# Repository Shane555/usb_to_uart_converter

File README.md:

2 layer USB to UART converter, bread and butter of embedded software for debug logs, flashing via serial etc. Gerber files can be used to generate PCB

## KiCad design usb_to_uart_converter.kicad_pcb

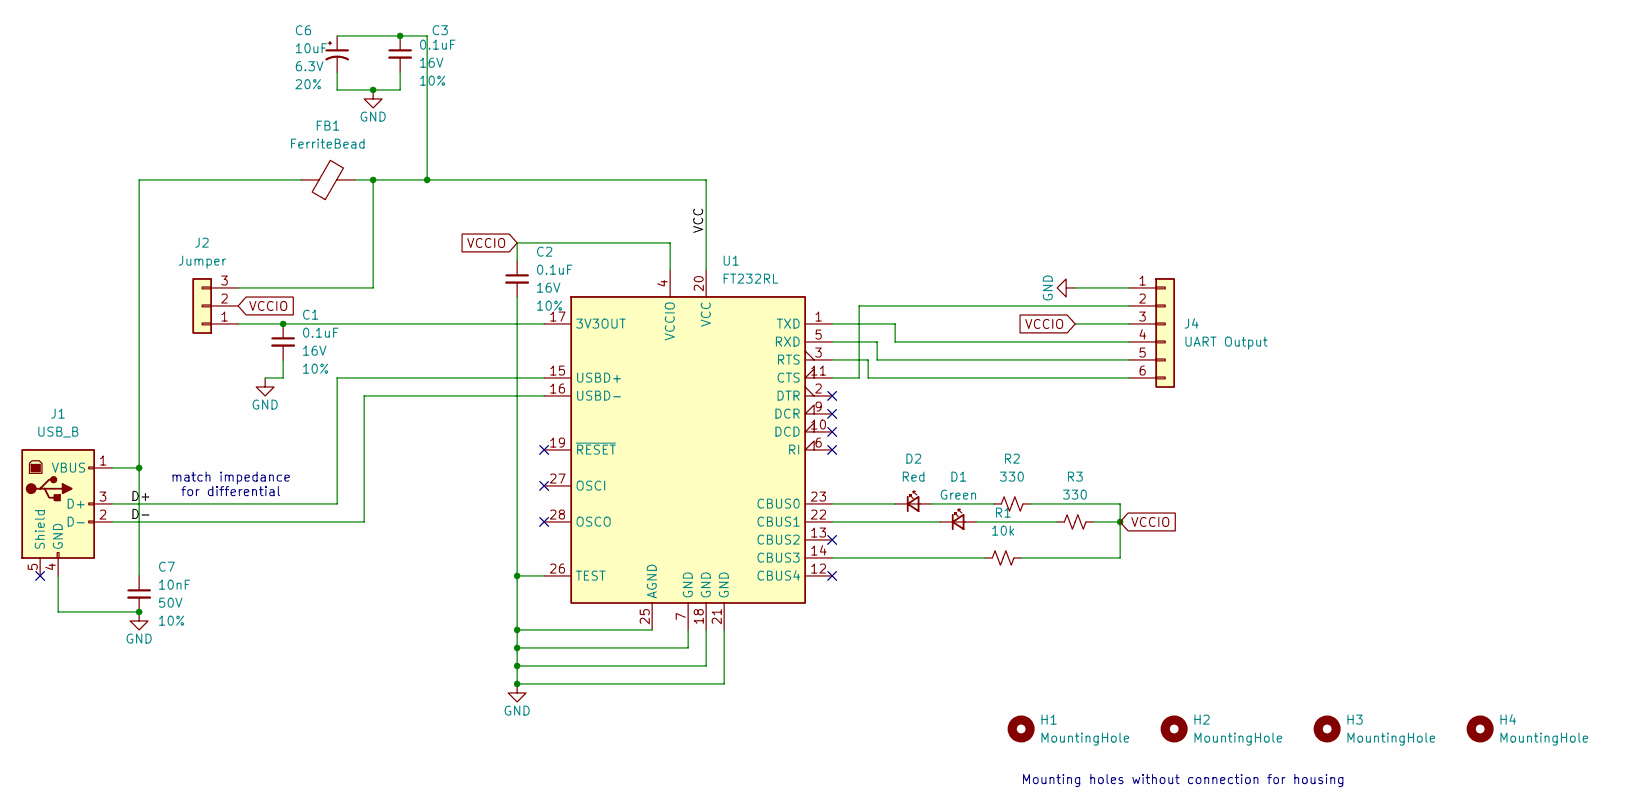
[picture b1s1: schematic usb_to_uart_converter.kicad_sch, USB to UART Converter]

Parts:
C1, C2, C3: 0.1uF; C_0402_1005Metric; Voltage 16V; Tolerance 10%
C6: 10uF; C_0603_1608Metric_Polar; Voltage 6.3V; Tolerance 20%
C7: 10nF; C_0603_1608Metric; Voltage 50V; Tolerance 10%
D1: Green; LED_1206_3216Metric_Green
D2: Red; LED_1206_3216Metric_Red
FB1: FerriteBead; LairdTech_28C0236-0JW-10
H1, H2, H3, H4: MountingHole; Standoff
J1: USB_B; USB_B_Amphenol_MUSB-D511_Vertical_Rugged
J2: Jumper; 1x03_P2.54mm
J4: UART Output; 1x06_P2.54mm_Locking
R1: 10k; R_0402_1005Metric
R2, R3: 330; R_0402_1005Metric
U1: FT232RL; SSOP-28_5.3x10.2mm_P0.65mm

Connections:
/D+: J1.3 (D+), U1.15 (USBD+)
/D-: J1.2 (D-), U1.16 (USBD-)
/VCC: C3.1, C6.1, FB1.2, J2.3, U1.20 (VCC)
GND: C1.2, C2.2, C3.2, C6.2, C7.2, J1.4 (GND), J4.1, U1.7 (GND), U1.18 (GND), U1.21 (GND), U1.25 (AGND), U1.26 (TEST)
unnamed: D1.2 (A), R3.1
unnamed: D1.1 (K), U1.22 (CBUS1)
unnamed: D2.2 (A), R2.1
unnamed: D2.1 (K), U1.23 (CBUS0)
unnamed: C7.1, FB1.1, J1.1 (VBUS)
unnamed: C1.1, J2.1, U1.17 (3V3OUT)
unnamed: J4.2, U1.11 (CTS)
unnamed: J4.4, U1.1 (TXD)
unnamed: J4.5, U1.5 (RXD)
unnamed: J4.6, U1.3 (RTS)
unnamed: R1.1, U1.14 (CBUS3)
VCCIO: C2.1, J2.2, J4.3, R1.2, R2.2, R3.2, U1.4 (VCCIO)

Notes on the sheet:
match impedance for differential
Mounting holes without connection for housing

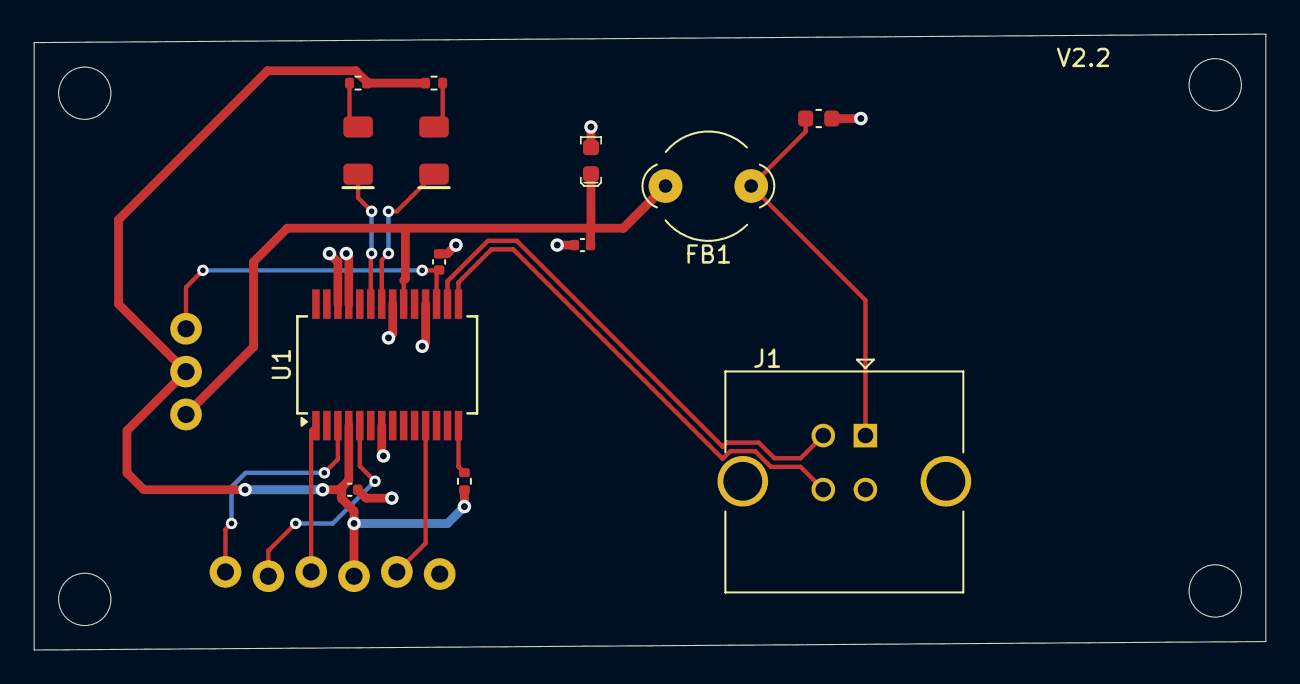
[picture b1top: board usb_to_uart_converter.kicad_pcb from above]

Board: 2 copper layers, 73.0 x 36.5 mm, 19 parts (0 on the bottom side), 16 nets.

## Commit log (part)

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2026-06-22 first commit of usb_uart_converter kicad
2026-06-22 generate gerber and drill files
2026-06-22 fix .gitignore and tracking backups
2026-06-22 Add initial project description and image to README
2026-06-23 Add image to README
    Added an additional image to the README for better visualization.
